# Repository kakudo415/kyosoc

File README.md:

# Kyosoc
61keys ortholinear keyboard inspired by HHKB.

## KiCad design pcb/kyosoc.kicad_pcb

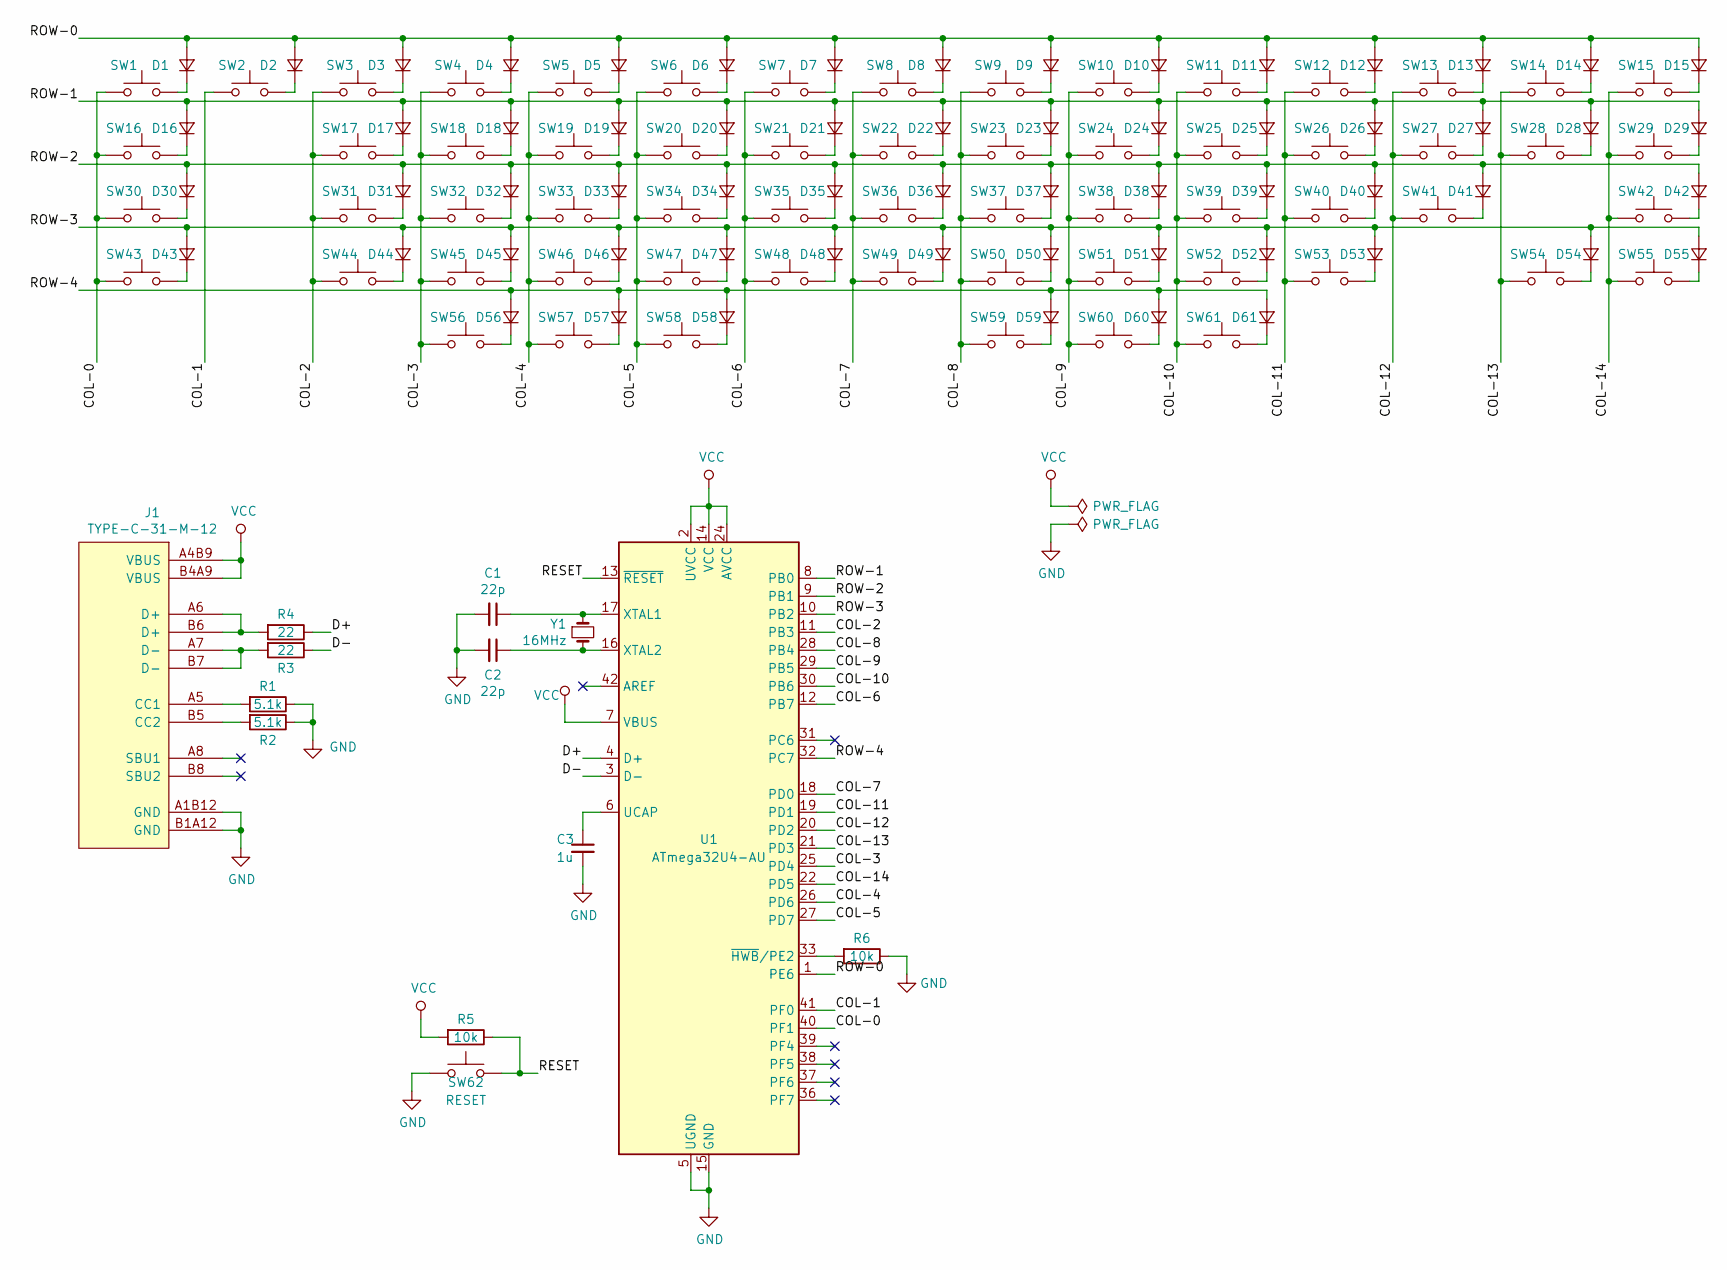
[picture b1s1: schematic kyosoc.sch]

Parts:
C1, C2: 22p; 1206-3216
C3: 1u; 1206-3216
D1, D2, D3, D4, D5, D6, D7, D8, D9, D10, D11, D12, D13, D14, D15, D16, D17, D18, D19, D20, D21, D22, D23, D24, D25, D26, D27, D28, D29, D30, D31, D32, D33, D34, D35, D36, D37, D38, D39, D40, D41, D42, D43, D44, D45, D46, D47, D48, D49, D50, D51, D52, D53, D54, D55, D56, D57, D58, D59, D60, D61: D_Small; 1N4148W
J1: TYPE-C-31-M-12
R1, R2: 5.1k; 1206-3216
R3, R4: 22; 1206-3216
R5, R6: 10k; 1206-3216
SW1, SW2, SW3, SW4, SW5, SW6, SW7, SW8, SW9, SW10, SW11, SW12, SW13, SW14, SW15, SW16, SW17, SW18, SW19, SW20, SW21, SW22, SW23, SW24, SW25, SW26, SW27, SW28, SW29, SW30, SW31, SW32, SW33, SW34, SW35, SW36, SW37, SW38, SW39, SW40, SW41, SW42, SW43, SW44, SW45, SW46, SW47, SW48, SW49, SW50, SW51, SW52, SW53, SW54, SW55, SW56, SW57, SW58, SW59, SW60, SW61: SW_Push; Cherry-MX-Kailh-Socket
SW62: RESET; Tact-Switch
U1: ATmega32U4-AU; TQFP44
Y1: 16MHz; Crystal-HC-49-S

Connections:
/COL-0: SW1.1, SW16.1, SW30.1, SW43.1, U1.40 (PF1)
/COL-1: SW2.1, U1.41 (PF0)
/COL-2: SW3.1, SW17.1, SW31.1, SW44.1, U1.11 (PB3)
/COL-3: SW4.1, SW18.1, SW32.1, SW45.1, SW56.1, U1.25 (PD4)
/COL-4: SW5.1, SW19.1, SW33.1, SW46.1, SW57.1, U1.26 (PD6)
/COL-5: SW6.1, SW20.1, SW34.1, SW47.1, SW58.1, U1.27 (PD7)
/COL-6: SW7.1, SW21.1, SW35.1, SW48.1, U1.12 (PB7)
/COL-7: SW8.1, SW22.1, SW36.1, SW49.1, U1.18 (PD0)
/COL-8: SW9.1, SW23.1, SW37.1, SW50.1, SW59.1, U1.28 (PB4)
/COL-9: SW10.1, SW24.1, SW38.1, SW51.1, SW60.1, U1.29 (PB5)
/COL-10: SW11.1, SW25.1, SW39.1, SW52.1, SW61.1, U1.30 (PB6)
/COL-11: SW12.1, SW26.1, SW40.1, SW53.1, U1.19 (PD1)
/COL-12: SW13.1, SW27.1, SW41.1, U1.20 (PD2)
/COL-13: SW14.1, SW28.1, SW54.1, U1.21 (PD3)
/COL-14: SW15.1, SW29.1, SW42.1, SW55.1, U1.22 (PD5)
/D+: R4.1, U1.4 (D+)
/D-: R3.1, U1.3 (D-)
/RESET: R5.1, SW62.2, U1.13 (~RESET)
/ROW-0: D1.2 (A), D2.2 (A), D3.2 (A), D4.2 (A), D5.2 (A), D6.2 (A), D7.2 (A), D8.2 (A), D9.2 (A), D10.2 (A), D11.2 (A), D12.2 (A), D13.2 (A), D14.2 (A), D15.2 (A), U1.1 (PE6)
/ROW-1: D16.2 (A), D17.2 (A), D18.2 (A), D19.2 (A), D20.2 (A), D21.2 (A), D22.2 (A), D23.2 (A), D24.2 (A), D25.2 (A), D26.2 (A), D27.2 (A), D28.2 (A), D29.2 (A), U1.8 (PB0)
/ROW-2: D30.2 (A), D31.2 (A), D32.2 (A), D33.2 (A), D34.2 (A), D35.2 (A), D36.2 (A), D37.2 (A), D38.2 (A), D39.2 (A), D40.2 (A), D41.2 (A), D42.2 (A), U1.9 (PB1)
/ROW-3: D43.2 (A), D44.2 (A), D45.2 (A), D46.2 (A), D47.2 (A), D48.2 (A), D49.2 (A), D50.2 (A), D51.2 (A), D52.2 (A), D53.2 (A), D54.2 (A), D55.2 (A), U1.10 (PB2)
/ROW-4: D56.2 (A), D57.2 (A), D58.2 (A), D59.2 (A), D60.2 (A), D61.2 (A), U1.32 (PC7)
GND: C1.2, C2.2, C3.2, J1.A1B12 (GND), J1.B1A12 (GND), R1.1, R2.1, R6.1, SW62.1, U1.5 (UGND), U1.15 (GND), U1.23 (GND), U1.35 (GND), U1.43 (GND)
unnamed: C1.1, U1.17 (XTAL1), Y1.1
unnamed: C2.1, U1.16 (XTAL2), Y1.2
unnamed: C3.1, U1.6 (UCAP)
unnamed: D1.1 (K), SW1.2
unnamed: D2.1 (K), SW2.2
unnamed: D3.1 (K), SW3.2
unnamed: D4.1 (K), SW4.2
unnamed: D5.1 (K), SW5.2
unnamed: D6.1 (K), SW6.2
unnamed: D7.1 (K), SW7.2
unnamed: D8.1 (K), SW8.2
unnamed: D9.1 (K), SW9.2
unnamed: D10.1 (K), SW10.2
unnamed: D11.1 (K), SW11.2
unnamed: D12.1 (K), SW12.2
unnamed: D13.1 (K), SW13.2
unnamed: D14.1 (K), SW14.2
unnamed: D15.1 (K), SW15.2
unnamed: D16.1 (K), SW16.2
unnamed: D17.1 (K), SW17.2
unnamed: D18.1 (K), SW18.2
unnamed: D19.1 (K), SW19.2
unnamed: D20.1 (K), SW20.2
unnamed: D21.1 (K), SW21.2
unnamed: D22.1 (K), SW22.2
unnamed: D23.1 (K), SW23.2
unnamed: D24.1 (K), SW24.2
unnamed: D25.1 (K), SW25.2
unnamed: D26.1 (K), SW26.2
unnamed: D27.1 (K), SW27.2
unnamed: D28.1 (K), SW28.2
unnamed: D29.1 (K), SW29.2
unnamed: D30.1 (K), SW30.2
unnamed: D31.1 (K), SW31.2
unnamed: D32.1 (K), SW32.2
unnamed: D33.1 (K), SW33.2
unnamed: D34.1 (K), SW34.2
unnamed: D35.1 (K), SW35.2
unnamed: D36.1 (K), SW36.2
unnamed: D37.1 (K), SW37.2
unnamed: D38.1 (K), SW38.2
unnamed: D39.1 (K), SW39.2
unnamed: D40.1 (K), SW40.2
unnamed: D41.1 (K), SW41.2
unnamed: D42.1 (K), SW42.2
unnamed: D43.1 (K), SW43.2
unnamed: D44.1 (K), SW44.2
unnamed: D45.1 (K), SW45.2
unnamed: D46.1 (K), SW46.2
unnamed: D47.1 (K), SW47.2
unnamed: D48.1 (K), SW48.2
unnamed: D49.1 (K), SW49.2
unnamed: D50.1 (K), SW50.2
unnamed: D51.1 (K), SW51.2
unnamed: D52.1 (K), SW52.2
unnamed: D53.1 (K), SW53.2
unnamed: D54.1 (K), SW54.2
unnamed: D55.1 (K), SW55.2
unnamed: D56.1 (K), SW56.2
unnamed: D57.1 (K), SW57.2
unnamed: D58.1 (K), SW58.2
unnamed: D59.1 (K), SW59.2
unnamed: D60.1 (K), SW60.2
unnamed: D61.1 (K), SW61.2
unnamed: J1.A5 (CC1), R1.2
unnamed: J1.A6 (D+), J1.B6 (D+), R4.2
unnamed: J1.A7 (D-), J1.B7 (D-), R3.2
unnamed: J1.B5 (CC2), R2.2
unnamed: R6.2, U1.33 (~HWB~/PE2)
VCC: J1.A4B9 (VBUS), J1.B4A9 (VBUS), R5.2, U1.2 (UVCC), U1.7 (VBUS), U1.14 (VCC), U1.24 (AVCC), U1.34 (VCC), U1.44 (AVCC)

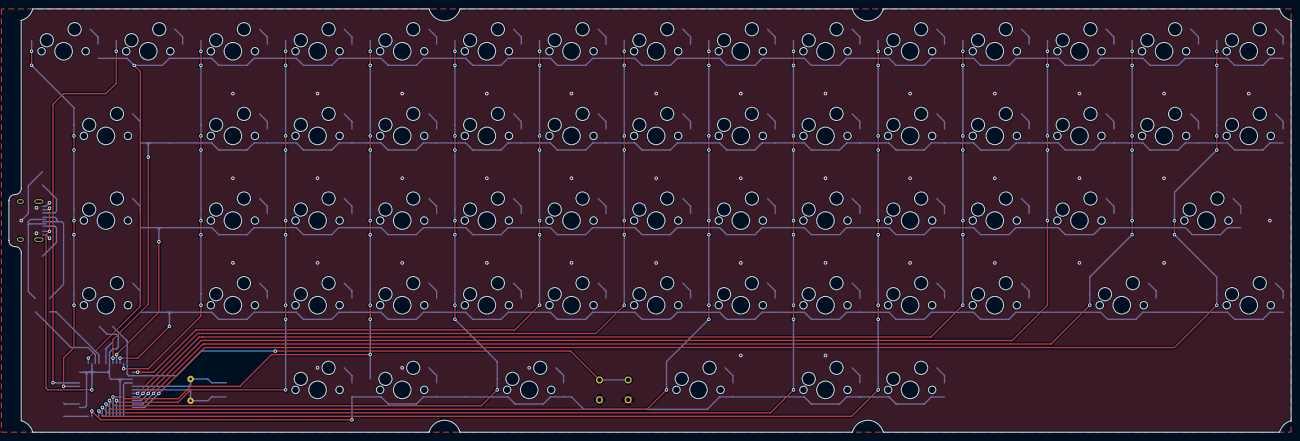
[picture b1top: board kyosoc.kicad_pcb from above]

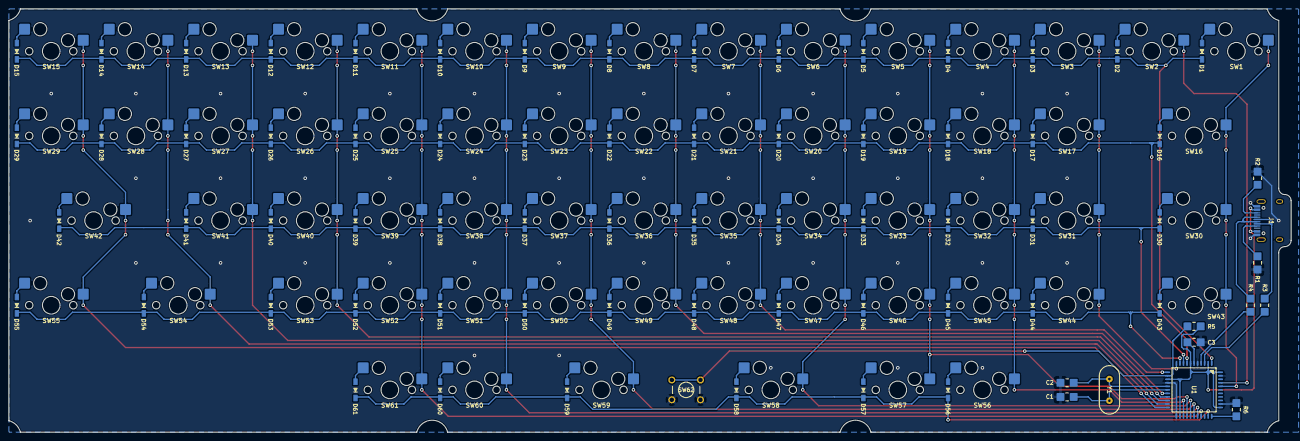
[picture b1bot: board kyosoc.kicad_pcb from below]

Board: 2 copper layers, 290.8 x 96.0 mm, 135 parts (74 on the bottom side), 94 nets.

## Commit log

2020-03-13 add description
2020-03-13 add ignore for kicad. copy from https://github.com/github/gitignore
2020-03-13 add kicad project
2020-03-14 add schematic
2020-03-14 add atmega32u4 & hc49s footprint
2020-03-14 add switch & kondensator footprint
2020-03-14 update footprint text to visible
2020-03-14 correspond to footprint (switches)
2020-03-14 add electrical pads
2020-03-14 put switches
2020-03-14 add outer lines
2020-03-14 update pcb size
2020-03-14 add holes and outer lines without stabilizer holes
2020-03-14 update more shrink pcb
2020-03-14 plate hole place update
2020-03-15 update plate design
2020-03-15 remove extra keys
2020-03-17 update with socket
2020-03-17 smd diode
2020-03-17 axial resistor
2020-03-17 hand solderble smd receptacle
2020-03-17 change to sandwitche style
2020-03-17 update layout
2020-03-20 update kondensator & resistor from tht to smd
2020-03-20 add exclusive symbol
2020-03-20 update smd
2020-03-20 wiring done without reset switch
2020-03-20 add bottom plate
2020-03-20 add tact-switch
2020-03-20 add gerber file
